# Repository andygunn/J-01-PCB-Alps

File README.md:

# J-01 Alps PCB

This is an Alps compatible PCB for the [J-01 keyboard](https://geekhack.org/index.php?topic=107597). Many thanks to Flex, the designer of the original PCB for their help with dimensions and layout compatibility. Additional thanks to Anjheos for the help with adding J-01 rev2 compatibility.

While it lacks support for MX switches, it has Alps switch support and the following additional features:
- Full bottom row support per the options in Via (see the following [Keyboard Layout](http://www.keyboard-layout-editor.com/#/gists/1aa1c3e0d55bc183d22bc74a1a26bc83) for more information).
- Normal, stepped, and 3800-style Capslock footprints.
- ISO Enter support - including for 1.25U vertical and horizontal rotation (Matias, DCS?), and 1.5U vertical orientation (Dell AT102).
- Some hand-solderable SMT component support, though the ATmega32U4-MU MCU is not hand-solderable.
- This PCB maintains PCB-mount MX stabilizer support, as most modern Alps keysets relased now have MX-style stabilizers. Using a plate with MX-style stabilizer cutouts will be requried to use those.

Some notable changes from the original J-01 rev1 PCB:
- Dual ground planes, instead of the GND / 5V plane on the original. It appears that the 5V ground plane on the original facilitated easier routing of the LED 5V signal, as well as power to the MCU. Since this Alps version of the PCB does not utilize in-switch LED footprints, this was changed.
- The spacing of the 6U spacebar stabilizer is different. I am not sure if the original PCB has these incorrect, or if I am using a different 6U spacebar stabilizer footprint, but that is a discrepancy.

## I provide this PCB without liability and without any guarantees regarding functionality, as expressed in the licenses under which this PCB is licensed.

Front render:

Back render:

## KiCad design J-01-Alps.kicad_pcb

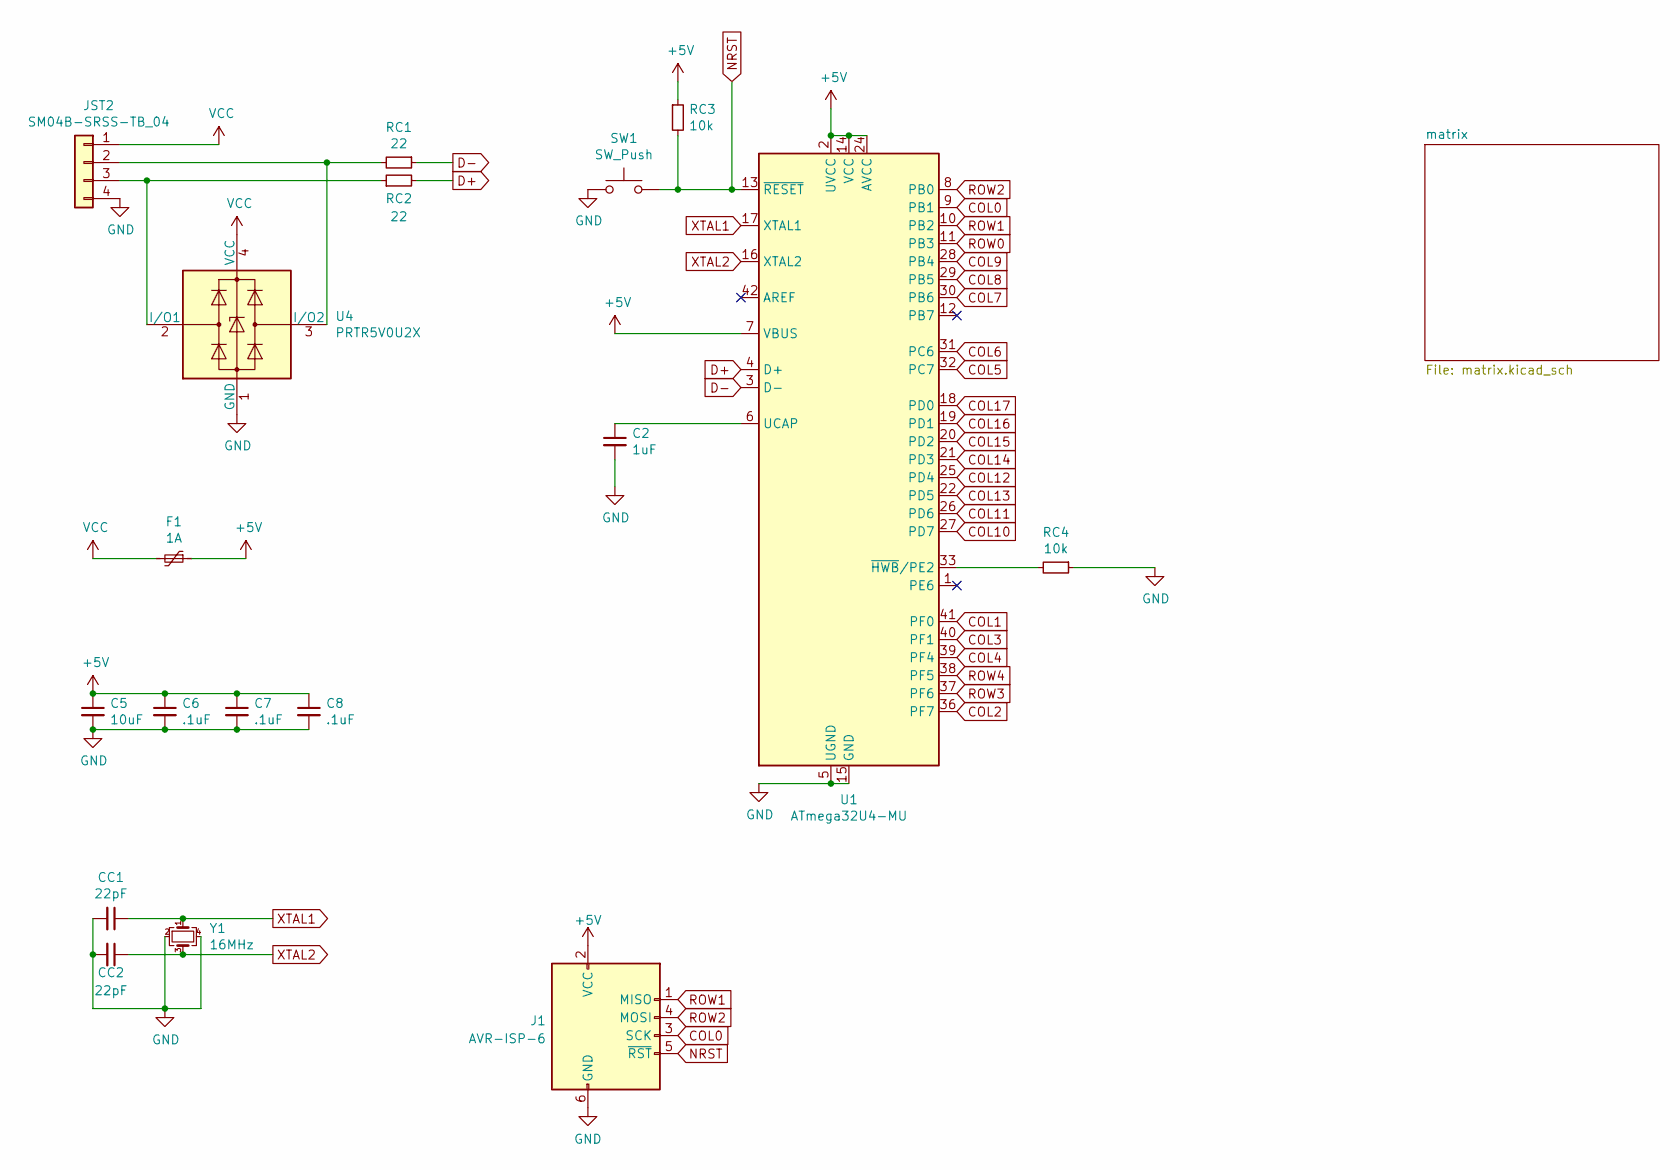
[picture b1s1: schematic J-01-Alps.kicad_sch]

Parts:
C2: 1uF; C_0603_1608Metric_Pad1.08x0.95mm_HandSolder; LCSC C15849
C5: 10uF; C_0603_1608Metric_Pad1.08x0.95mm_HandSolder; LCSC C19702
C6, C7, C8: .1uF; C_0603_1608Metric_Pad1.08x0.95mm_HandSolder; LCSC C14663
CC1, CC2: 22pF; C_0603_1608Metric_Pad1.08x0.95mm_HandSolder; LCSC C1653
F1: 1A; Fuse_1206_3216Metric_Pad1.42x1.75mm_HandSolder; LCSC C315893
J1: AVR-ISP-6; PinHeader_2x03_P2.54mm_Vertical
JST2: SM04B-SRSS-TB_04; JST_SH_SM04B-SRSS-TB_1x04-1MP_P1.00mm_Horizontal; LCSC C160404
RC1, RC2: 22; R_0603_1608Metric_Pad0.98x0.95mm_HandSolder; LCSC C23345
RC3, RC4: 10k; R_0603_1608Metric_Pad0.98x0.95mm_HandSolder; LCSC C25804
SW1: SW_Push; SKQGADE010
U1: ATmega32U4-MU; QFN-44-1EP_7x7mm_P0.5mm_EP5.15x5.15mm
U4: PRTR5V0U2X; SOT143B; LCSC C12333
Y1: 16MHz; Crystal_SMD_3225-4Pin_3.2x2.5mm_HandSoldering; LCSC C255906

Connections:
+5V: C5.1, C6.1, C7.1, C8.1, F1.1, J1.2 (VCC), RC3.1, U1.2 (UVCC), U1.7 (VBUS), U1.14 (VCC), U1.24 (AVCC), U1.34 (VCC), U1.44 (AVCC)
COL0: J1.3 (SCK), U1.9 (PB1); also elsewhere on the board
COL1: U1.41 (PF0); also elsewhere on the board
COL2: U1.36 (PF7); also elsewhere on the board
COL3: U1.40 (PF1); also elsewhere on the board
COL4: U1.39 (PF4); also elsewhere on the board
COL5: U1.32 (PC7); also elsewhere on the board
COL6: U1.31 (PC6); also elsewhere on the board
COL7: U1.30 (PB6); also elsewhere on the board
COL8: U1.29 (PB5); also elsewhere on the board
COL9: U1.28 (PB4); also elsewhere on the board
COL10: U1.27 (PD7); also elsewhere on the board
COL11: U1.26 (PD6); also elsewhere on the board
COL12: U1.25 (PD4); also elsewhere on the board
COL13: U1.22 (PD5); also elsewhere on the board
COL14: U1.21 (PD3); also elsewhere on the board
COL15: U1.20 (PD2); also elsewhere on the board
COL16: U1.19 (PD1); also elsewhere on the board
COL17: U1.18 (PD0); also elsewhere on the board
D+: RC2.2, U1.4 (D+)
D-: RC1.1, U1.3 (D-)
GND: C2.2, C5.2, C6.2, C7.2, C8.2, CC1.2, CC2.2, J1.6 (GND), JST2.4, RC4.1, SW1.1, U1.5 (UGND), U1.15 (GND), U1.23 (GND), U1.35 (GND), U1.43 (GND), U4.1 (GND), Y1.2, Y1.4
NRST: J1.5 (~RST), RC3.2, SW1.2, U1.13 (~RESET)
unnamed: C2.1, U1.6 (UCAP)
unnamed: JST2.2, RC1.2, U4.3 (I/O2)
unnamed: JST2.3, RC2.1, U4.2 (I/O1)
unnamed: RC4.2, U1.33 (~HWB/PE2)
ROW0: U1.11 (PB3); also elsewhere on the board
ROW1: J1.1 (MISO), U1.10 (PB2); also elsewhere on the board
ROW2: J1.4 (MOSI), U1.8 (PB0); also elsewhere on the board
ROW3: U1.37 (PF6); also elsewhere on the board
ROW4: U1.38 (PF5); also elsewhere on the board
VCC: F1.2, JST2.1, U4.4 (VCC)
XTAL1: CC1.1, U1.17 (XTAL1), Y1.1
XTAL2: CC2.1, U1.16 (XTAL2), Y1.3
